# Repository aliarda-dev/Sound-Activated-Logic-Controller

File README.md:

***Sound Activated Logic Controller***

Bu proje, ses tetiklemeli bir kontrol sistemi prototipidir. Mikrofon sensöründen alınan sinyal işlenerek, alkış gibi ani seslere göre LED'ler farklı durumlara geçirilir.

***Donanım***
- Arduino Uno
- Sound Sensor (mikrofon modülü)(FC-04)
- Kırmızı, Sarı, Yeşil LED'ler

---

***Nasıl Çalışır?***
- Sensörden gelen analog değer okunur
- Belirlenen threshold değeri aşılırsa tetikleme oluşur
- Yanlış tetiklemeleri azaltmak için 200ms debounce uygulanır
- 1 saniyelik zaman penceresinde algılanan alkış sayısına göre sistem durumu değiştirilir
- LED kontrolü switch-case yapısı ile gerçekleştirilir
- delay() yerine millis() kullanılarak sistem non-blocking şekilde çalışır

---

***Geliştirme Fikirleri***
- Adaptive threshold
- PWM ile ses şiddetine göre parlaklık kontrolü

---

***Not***

Projenin USB C 2.0 kullanılarak yapılacak halinin pcb tasarımı ve gerekli gerber dosyaları yüklendi. PCB tasarımı esnasında fark ettiğim bir eksiğim de şu oldu, analog veya dijital binleri arduino üzerine rastgele yerleştirmemek çünkü trace çekerken zorlanmama sebep oluyor.Ayrıca bu projenin pcb tasarımında gnd bakır düzlemini (GND Plane) kullandım.

- 🎥 Proje Demo
  
Projenin çalışma videosunu aşağıdan izleyebilirsiniz.

https://github.com/user-attachments/assets/4fc10618-45ed-4bd7-b765-5fb663c96ab2

-📷 Proje PCB Medyası

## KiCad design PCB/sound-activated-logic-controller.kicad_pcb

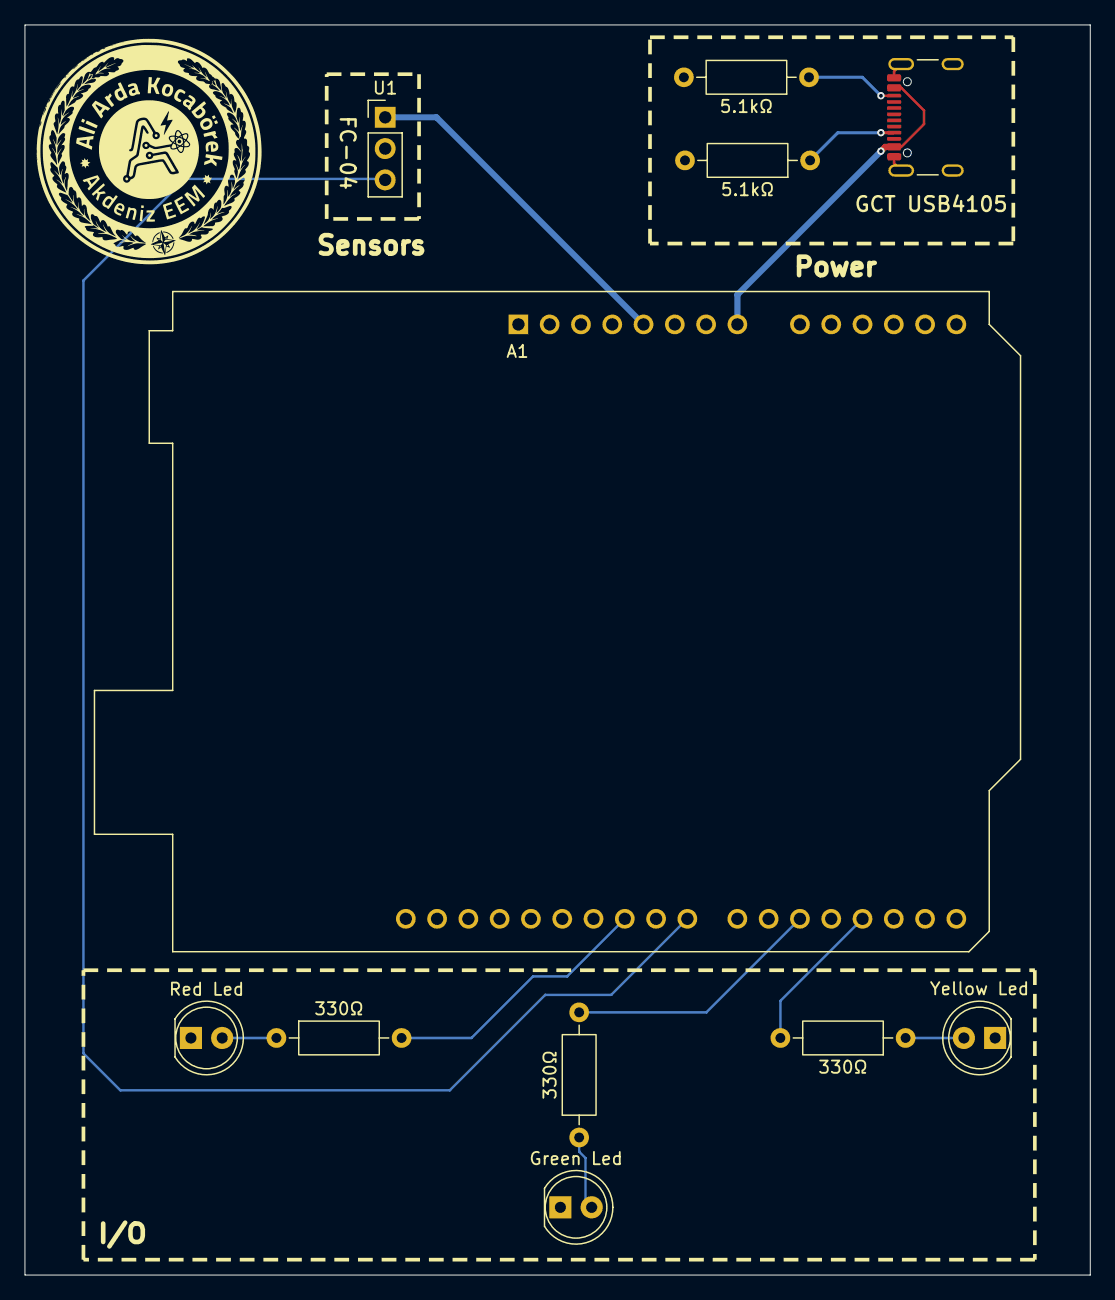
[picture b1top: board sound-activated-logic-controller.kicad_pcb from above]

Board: 2 copper layers, 86.5 x 101.5 mm, 11 parts (0 on the bottom side), 12 nets.

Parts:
5.1kΩ, 5.1kΩ#2: 5.1kΩ; R_Axial_DIN0207_L6.3mm_D2.5mm_P10.16mm_Horizontal
330Ω, 330Ω#2, 330Ω#3: 330R; R_Axial_DIN0207_L6.3mm_D2.5mm_P10.16mm_Horizontal
A1: Arduino_UNO_R3
Green Led: LED; LED_D5.0mm
J1: USB_C_Receptacle_USB2.0_16P; USB_C_Receptacle_GCT_USB4105-xx-A_16P_TopMnt_Horizontal
Red Led: LED; LED_D5.0mm
U1: FC-04-SOUND
Yellow Led: Yellow Led; LED_D5.0mm

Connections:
3: 330Ω#3.2, A1.18 (D3)
5: 330Ω#2.2, A1.20 (D5)
5V: A1.5 (+5V), U1.1 (VCC)
8: A1.23 (D8), U1.3 (OUT)
10: 330Ω.2, A1.25 (D10)
GND: 5.1kΩ.2, 5.1kΩ#2.2, A1.6 (GND), A1.7 (GND), A1.29 (GND), Green Led.1 (K), J1.A1 (GND), J1.A12 (GND), J1.B1 (GND), J1.B12 (GND), J1.SH (SHIELD), Red Led.1 (K), U1.2 (GND), Yellow Led.1 (K)
unnamed: 330Ω.1, Red Led.2 (A)
unnamed: 330Ω#3.1, Yellow Led.2 (A)
unnamed: 330Ω#2.1, Green Led.2 (A)
unnamed: 5.1kΩ#2.1, J1.A5 (CC1)
unnamed: 5.1kΩ.1, J1.B5 (CC2)
VIN: A1.8 (VIN), J1.A4 (VBUS), J1.A9 (VBUS), J1.B4 (VBUS), J1.B9 (VBUS)

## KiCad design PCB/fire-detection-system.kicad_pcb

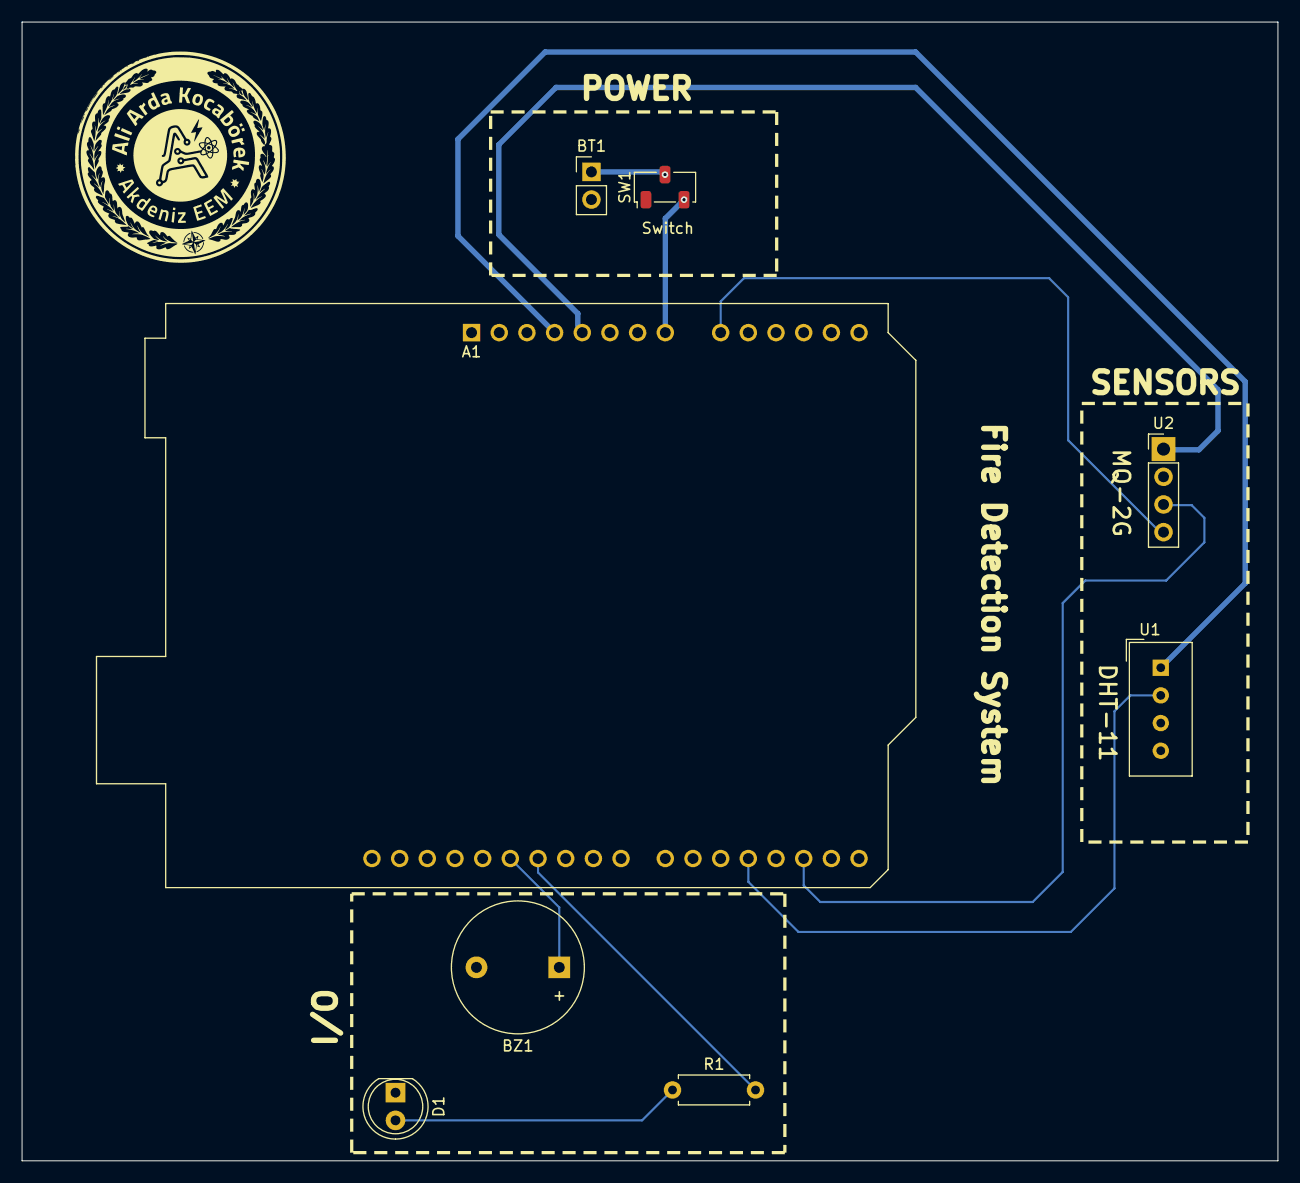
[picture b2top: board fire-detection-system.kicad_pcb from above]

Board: 2 copper layers, 115.2 x 104.5 mm, 8 parts (0 on the bottom side), 11 nets.

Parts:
A1: Arduino_UNO_R3
BT1: 9V; PinHeader_1x02_P2.54mm_Vertical
BZ1: Buzzer; Buzzer_12x9.5RM7.6
D1: LED; LED_D5.0mm
R1: 330R; R_Axial_DIN0207_L6.3mm_D2.5mm_P7.62mm_Horizontal
SW1: SW_Nidec_CAS-120A1; Nidec_Copal_CAS-120A
U1: DHT11; Aosong_DHT11_5.5x12.0_P2.54mm
U2: mq2-gas-sensor

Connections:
3.3V: A1.4 (3V3), U1.1 (VDD)
5V: A1.5 (+5V), U2.1 (VCC)
A0-MQ2: A1.9 (A0), U2.4 (AO)
BO: A1.27 (D12), BZ1.1 (+)
DATA-STH11: A1.19 (D4), U1.2 (DATA)
DO-MQ2: A1.17 (D2), U2.3 (DO)
GND: A1.6 (GND), A1.7 (GND), A1.29 (GND), BT1.2 (-), BZ1.2 (-), D1.1 (K), U1.4 (GND), U2.2 (GND)
LED: A1.26 (D11), R1.2
unnamed: BT1.1 (+), SW1.2 (B)
unnamed: D1.2 (A), R1.1
VCC: A1.8 (VIN), SW1.3 (A)

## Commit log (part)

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2026-06-11 About Sound Activated Logic Controller Project
    Added detailed project description, system architecture, technical principles, engineering insights, and future vision for the Sound Activated Logic Controller.
2026-06-11 About Sound Activated Logic Controller Project
2026-06-11 Media
2026-06-11 Added Media
2026-06-11 Arduino IDE Code For Logic Controller Project
